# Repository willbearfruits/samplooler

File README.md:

# Samplooler

A small looper you play by tilting it. Hold the button and make a sound; let go and it loops. Tip
the box forward and the loop runs faster, tip it back and it runs backwards, roll it sideways for a
tape delay or a stutter.

> PHOTO: the Stack in a hand, tipped forward, screen lit (media/photos/stack-hand.jpg)

**[Try it and flash it from the browser](https://willbearfruits.github.io/samplooler/)** ·
[Manual](docs/MANUAL.md) · [Build one](docs/BUILD.md) · [Get one](#get-one)

The loop is a tape between two reels, and a small operator runs on it, as fast as you tip the box. The screen
above is the firmware's own drawing code, run on a computer.

> VIDEO: someone playing a Stack, filmed, with its sound, about 60 s

## What it does

| | |
| - | - |
| Record | Hold the button and make a sound, up to 20 s at 32 kHz. Let go and it loops. |
| Tilt | Forward plays faster, back plays backwards. Snap rounds the speed to octaves and fifths. |
| Roll | Left adds a tape delay, right a stutter. |
| Modes | TAPE (speed and pitch move together) and GRAIN (they move apart). |
| Voice | Optional: SING's 18 voices on the input before it records (autotune, harmonies, choir, vocoder, echo). |
| Speaker | Can be switched off, so only the line out plays, when the speaker feeds back into the mic. |
| Slots | 8 loops saved on the board, kept when you update it. |
| Together | Over the radio with the other instruments: a take sets their tempo or lands on their beat; key and scale are shared. |
| With a computer | USB MIDI and a USB sound card on one cable, and a VST3 plugin that shows and sets everything. |
| Other instruments | More firmwares for the same box: a breakcore-to-doom machine, a singing Buddha with a wall of amps, a flute you blow. |

## Other instruments

The same Stack can be flashed with [WRECK](instruments/wreck), [MANTRA](instruments/mantra) or
[HUFF](instruments/huff), and flashed back. Install them from the [page](https://willbearfruits.github.io/samplooler/#instruments)
or with the desktop app in [app/](app/). More are in progress ([instruments/](instruments/), [ROADMAP.md](ROADMAP.md)).
Anyone can add one ([CONTRIBUTING.md](CONTRIBUTING.md)).

## Get one

- **Buy one**: built by hand in Haifa. Write and ask about price and shipping:
  [Dogme84@gmail.com](mailto:Dogme84@gmail.com?subject=Samplooler) ·
  [WhatsApp](https://wa.me/972539263808).
- **Build it in the workshop**: the [ESP32 workshop](https://willbearfruits.github.io/serious-shit/workshop-esp32.html),
  7 meetings at MEZO, Haifa, 2,200 ₪, kit included.
- **Build it yourself**: order the boards, solder the modules on, flash it: [docs/BUILD.md](docs/BUILD.md).

## Status

Early. The current Stack is rev C: it has been made and runs the firmware (screen, microphone, tilt,
line out and USB MIDI/audio work). The board files here are rev D, which is being tested now (October
2026); rev C's files are at the git tag `checkpoint/boards-rev-c`. The three other instruments on the list have run
on a board; eight more are in progress. What comes next is in [ROADMAP.md](ROADMAP.md). Reports of builds, good or
bad, are welcome in the issues.

## What is where

| Path | What |
| - | - |
| [ROADMAP.md](ROADMAP.md) | what is done and what comes next |
| [docs/](docs/) | the manual and the build guide |
| [firmware/](firmware/) | the Samplooler's ESP-IDF 5.5 project |
| [instruments/](instruments/) | the other instruments, each a complete ESP-IDF project |
| [core/](core/) | the code the instruments share |
| [hardware/](hardware/) | the Stack's schematics, boards and JLCPCB order files |
| [plugin/](plugin/) | the VST3 and standalone plugin (JUCE) |
| [app/](app/) | the desktop app: the library, one-click install of any instrument on a board, and the Samplooler back |
| [media/](media/) | pictures and screen grabs |
| [site/](site/) | the project page and the browser flasher |
| [tools/](tools/) | `flash.sh`, `sl_midi.py` (log and MIDI from a shell), `release.sh`, `library.py` |

## Licence

- Firmware, instruments and tools: GPL-3.0 ([LICENSE](LICENSE)).
- Plugin: AGPL-3.0, as JUCE requires ([plugin/LICENSE](plugin/LICENSE)).
- Circuit boards, docs and pictures: CC BY-SA 4.0 ([hardware/LICENSE](hardware/LICENSE)).

---

Part of [Serious S.H.I.T.](https://willbearfruits.github.io/): instruments, tools and workshops made in Haifa by
Yaniv Schonfeld (Willbear). If Samplooler is useful to you, [support it on Patreon](https://www.patreon.com/Seriousshit).

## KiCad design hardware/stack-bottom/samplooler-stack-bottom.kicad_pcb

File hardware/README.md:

# Samplooler Stack boards

Two boards, 94 x 46 mm, 11 mm apart on M3 standoffs, made as one 94 x 94 mm panel. The bottom board carries every
module, the bare joystick and the encoder. The top board hangs the OLED and the microphone underneath it, seen and
heard through a window and a port. The modules sit on straight headers; the pins follow `firmware/main/pins.h`.

Rev C is the current board: it was made and runs the firmware, and the screen, microphone, tilt, line out and USB
MIDI/audio work. Its files are at the git tag `checkpoint/boards-rev-c`. Rev C has the KY-023 joystick on its own
little board, DAC strap jumpers, and the OLED and the mic on top of the top board. The files here are rev D, which
is being tested now (October 2026).

Both rev D boards pass ERC and DRC with no findings; the reports are in each project folder. How to build one is in
[docs/BUILD.md](../docs/BUILD.md).

## What is on each board

| Board | Ref | Part | Notes |
| - | - | - | - |
| Bottom | U1 | ESP32-S3 SuperMini (ESP32-S3FH4R2) | 20 pogo pads underneath |
| Bottom | U2 | GY-PCM5102 DAC with 3.5 mm jack | control pins tied on the board through its 9-pin row |
| Bottom | U4 | GY-521 (MPU-6050) | the tilt sensor |
| Bottom | U5 | PS2-style joystick, bare (the part on a KY-023) | its click is the record button (GPIO 3); X and Y go to GPIO 2 and 1, unused by the firmware |
| Bottom | SW1 | EC11 encoder with push, 25 mm shaft | |
| Bottom | J1 | 2 x 4 socket | the link to the top board: I2C for the OLED, I2S for the mic, GND |
| Bottom | J2 | header for a MAX98357A amp | optional |
| Bottom | J3 | Qwiic, JST-SH 4-pin | optional |
| Bottom | J4, J5 | EXP A, EXP B | breakouts, below |
| Bottom | C1 to C3 | 10 µF, 10 µF, 100 nF, 0805 | |
| Bottom | R1, R2 | 4.7 k I2C pull-ups, 0805 | not fitted |
| Top | U1 | SSD1306 0.96" OLED, 4 pins | underneath, seen through a window |
| Top | U2 | INMP441 microphone | underneath, hears through a 1.5 mm port |
| Top | J1 | 2 x 4 header | underneath, into the bottom board's socket |
| Top | JP1, JP2 | OLED pin-order jumpers | |
| Top | C1 to C3 | 10 µF, 100 nF, 100 nF, 0805 | |

The top board has openings for the stick, the encoder shaft, BOOT and RST. The full parts list with quantities is
in [docs/BUILD.md](../docs/BUILD.md#parts).

## Extras

| Extra | What it is |
| - | - |
| Pogo pins | Spring pins on the bottom board touch the SuperMini's 20 underside pads, for 20 more GPIOs: 14 to 18, 21, 33 to 42 and 45 to 48. They only feed the breakouts; the Samplooler does not need them. |
| EXP A, EXP B | Every GPIO the design does not use, on labelled 2.54 mm pads in the middle of the bottom board, under the top board. Solder wires, or fit plain straight headers (2.5 mm plastic plus about 6 mm of pin clears the 11 mm gap) and connect them before the top board goes on. There is no room for Dupont housings between the boards. |
| Qwiic | JST-SH, 3.3 V I2C, for sensors and add-ons. |
| Amp header | For the optional MAX98357A (Adafruit 3006 pin order), which hangs off the left edge. It takes 5 V. |
| OLED pin-order jumpers | JP1 and JP2 swap GND and VCC, so both common OLED pin orders fit without rework. |
| DAC pins tied | FLT, DEMP and FMT to ground, XSMT to the DAC's own 3.3 V, through the DAC's 9-pin row. No straps to set. |

EXP A, upper row, left to right; pin 1 is top right:

| | | | | | | | |
| - | :-: | :-: | :-: | :-: | :-: | :-: | :-: |
| top | GND | 48 | 47 | 46 | 42 | 40 | 43 TX |
| bottom | 3V3 | 37 | 38 | 45 | 41 | 39 | 44 RX |

EXP B, lower row, left to right; pin 1 is top right:

| | | | | | | | |
| - | :-: | :-: | :-: | :-: | :-: | :-: | :-: |
| top | GND | GND | 36 | 17 | 15 | 18 | 33 |
| bottom | 5V | 3V3 | 35 | 16 | 14 | 21 | 34 |

The numbers are not in order because each row takes the lines in the order they come out from under the SuperMini.

The SuperMini sits on its headers 2.5 mm above the board, and its pads are 1.753 mm apart down each column, so the
pogo pin's base width matters more than its height. You only need pins on the pads you use. Clamp the module while
you solder its headers: the springs push it up.

| Pogo pin | Fits | Where |
| - | - | - |
| Same Sky CPG-15-SMT-TR | every pad | DigiKey, Same Sky; not at LCSC |
| SMD pogo pins with a 2 mm flange, e.g. YIYUAN (LCSC C5221287, C2988082, C5157384) | every other pad only | LCSC |
| Harwin P70 (LCSC C17702549), Mill-Max 0900 | only with a spacer: they don't match the 2.5 mm gap | |

Two checks on your own SuperMini. The silkscreen of the pad column next to TX/RX says 48 at the top and 39 at the
bottom, but nologo's schematic shows the reverse: meter it in diode mode, the pad marked 48 lights the module's RGB
LED. And GPIO 45 and 46 must not be pulled high at power-up (45 high sets the flash to 1.8 V).

## Pictures

| Bottom board | Top board |
| - | - |
|  |  |
|  |  |

| From the nose | The panel |
| - | - |
|  |  |

The back of the panel: [images/panel-stack-back.png](images/panel-stack-back.png). All renders, from KiCad.

> PHOTO: the rev D boards as made, both faces, bare and with the modules on

## Ordering from JLCPCB

The two boards come as one panel, 94 x 94 mm, so they fit JLC's 100 x 100 mm price. They are joined by three 5 mm
tabs across a 2 mm slot, each tab with a row of 0.5 mm mouse-bite holes on both sides: snap them apart and file the
nubs flush.

Upload `fab/samplooler-panel-stack-jlcpcb.zip`. Also set Panel by Customer, and Different Design to 2. JLC counts
two designs on one panel as a different-design order and may charge for it; check the price before you pay.

| Setting | Value |
| - | - |
| Layers | 2 |
| Thickness | 1.6 mm FR-4 |
| Surface | HASL lead-free, or ENIG |
| Tracks / vias | 0.25 mm signal, 0.5 to 0.6 mm power, 0.6/0.3 mm vias, 0.5 mm to the edge: the standard process |
| Order number | "Specify a location": each board carries a `JLCJLCJLCJLC` text on its back (the panel has two; JLC uses one) |

The encoder's mounting lugs are plated slots, which the standard process covers. The openings for the stick, the
shaft, BOOT and RST, and the screen's window, are routed from the outline.

The SMD parts are the 0805 capacitors, the two unfitted 0805 resistors and the pogo pins. The capacitors are easy
by hand. If you'd rather have JLC fit them, the BOM and CPL files are in JLC's SMT format. The panel's pair names
each part with its board's prefix (`BC1` is the bottom board's C1, `TC1` the top's), and JLC may want tooling rails
added for assembly, which the panel doesn't have.

| File in `fab/` | What |
| - | - |
| [samplooler-panel-stack-jlcpcb.zip](fab/samplooler-panel-stack-jlcpcb.zip) | Gerbers and drill files for the panel, both boards. The one to upload. |
| [samplooler-panel-stack-bom.csv](fab/samplooler-panel-stack-bom.csv), [-cpl.csv](fab/samplooler-panel-stack-cpl.csv) | the panel's capacitors, for JLC assembly |
| [samplooler-stack-bottom-jlcpcb.zip](fab/samplooler-stack-bottom-jlcpcb.zip), [samplooler-stack-top-jlcpcb.zip](fab/samplooler-stack-top-jlcpcb.zip) | each board on its own |
| [samplooler-stack-bottom-bom.csv](fab/samplooler-stack-bottom-bom.csv), [-cpl.csv](fab/samplooler-stack-bottom-cpl.csv) | the bottom board's capacitors |
| [samplooler-stack-top-bom.csv](fab/samplooler-stack-top-bom.csv), [-cpl.csv](fab/samplooler-stack-top-cpl.csv) | the top board's capacitors |
| [samplooler-stack-bottom-schematic.pdf](fab/samplooler-stack-bottom-schematic.pdf), [samplooler-stack-top-schematic.pdf](fab/samplooler-stack-top-schematic.pdf) | the schematics |

## Before you order: measure these

Cheap modules differ between sellers. Where sources disagreed, the pads sit at the midpoint and the drills are
opened up. A minute with calipers confirms these:

| Check | Designed for | Tolerance built in |
| - | - | - |
| SuperMini: distance between its two pin rows | 15.33 mm (sources say 15.24 to 15.46) | 1.1 mm drills fit either |
| DAC: the 9-pin row (FLT to LROUT) against the 6-pin header | 6.475 mm in, 0.65 mm up from SCK | 1.2 mm drills |
| OLED: pin order | GND VCC SCL SDA | the jumpers swap GND and VCC |
| OLED: active area against the header | 21.7 x 10.9 mm, its top edge 4.5 mm below the pins | window 1.5 mm larger all round (24.7 x 13.9 mm) |
| Joystick: switch legs | rows 7.81 and 12.6 mm from the stick, 6.35 mm apart across | 1.2 mm drills (Adafruit's footprint says 8.0 / 12.5, SparkFun's 7.62 / 12.7) |
| Joystick: from the bottom of its frame to the underside of the cap | 20 mm, an estimate: no maker drawing found | at full tilt (25 degrees) the cap's rim stays over the top board from about 18.5 mm (20 mm if it tilts 30 degrees); lower, and it can touch the board |

## Opening them in KiCad

KiCad 10. Each folder is a project; the module symbols, footprints and 3D models come from `lib/` through the
projects' own library tables.

| Folder | What |
| - | - |
| [stack-bottom/](stack-bottom/) | the bottom board: schematic, PCB, ERC and DRC reports |
| [stack-top/](stack-top/) | the top board: the same |
| [panel-stack/](panel-stack/) | the two boards on one panel, as ordered |
| [lib/](lib/) | the symbol, footprint and 3D-model libraries for the modules |

## Licence

The board files, renders and fab outputs are CC BY-SA 4.0 ([LICENSE](LICENSE)).

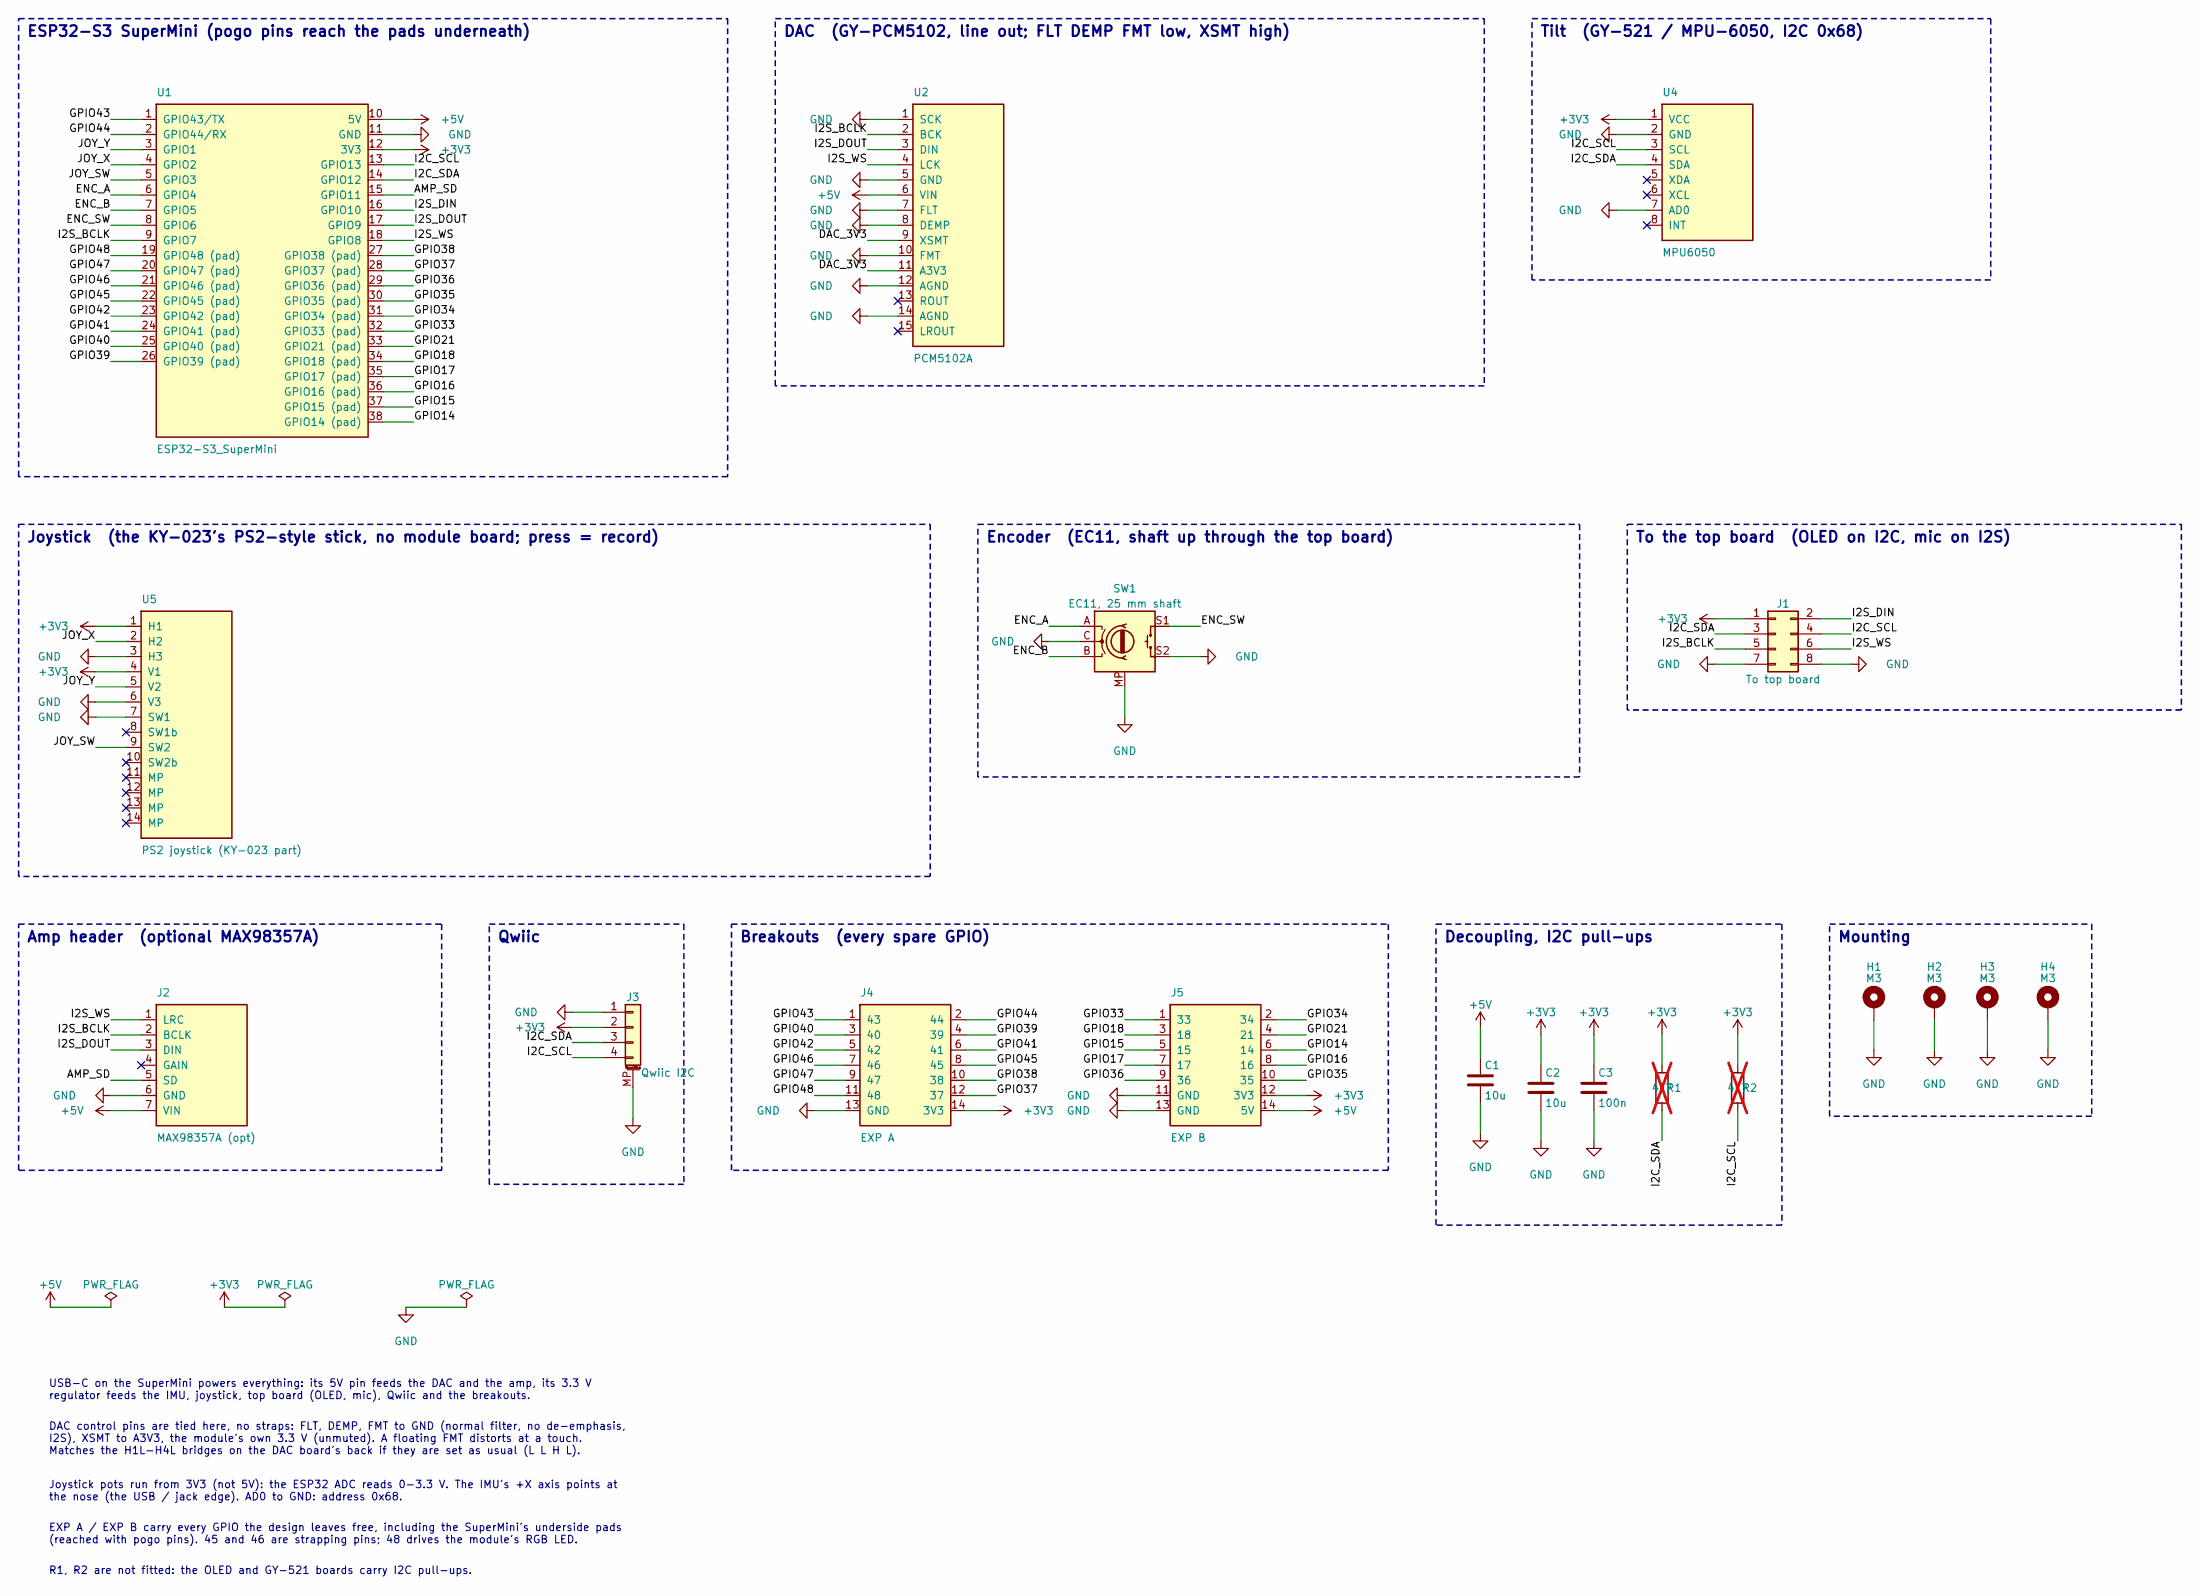
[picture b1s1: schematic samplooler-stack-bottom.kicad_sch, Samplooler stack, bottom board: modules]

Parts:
C1, C2: 10u; C_0805_2012Metric; LCSC C15850
C3: 100n; C_0805_2012Metric; LCSC C49678
H1, H2, H3, H4: M3; MountingHole_3.2mm_M3_Pad_Via
J1: To top board; PinSocket_2x04_P2.54mm_Vertical
J2: MAX98357A (opt); MAX98357A_Breakout
J3: Qwiic I2C; JST_SH_SM04B-SRSS-TB_1x04-1MP_P1.00mm_Horizontal
J4: EXP A; EXP_A_2x7_Stack
J5: EXP B; EXP_B_2x7_Stack
R1, R2: 4k7; R_0805_2012Metric; LCSC C17673; not fitted
SW1: EC11, 25 mm shaft; RotaryEncoder_Alps_EC11E-Switch_Vertical_H20mm
U1: ESP32-S3_SuperMini
U2: PCM5102A; GY-PCM5102
U4: MPU6050; GY-521_MPU6050
U5: PS2 joystick (KY-023 part); PS2_Joystick

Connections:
+3V3: C2.1, C3.1, J1.1, J3.2, J4.14 (3V3), J5.12 (3V3), R1.1, R2.1, U1.12 (3V3), U4.1 (VCC), U5.1 (H1), U5.4 (V1)
+5V: C1.1, J2.7 (VIN), J5.14 (5V), U1.10 (5V), U2.6 (VIN)
/AMP_SD: J2.5 (SD), U1.15 (11)
/DAC_3V3: U2.9 (XSMT), U2.11 (A3V3)
/ENC_A: SW1.A, U1.6 (4)
/ENC_B: SW1.B, U1.7 (5)
/ENC_SW: SW1.S1, U1.8 (6)
/GPIO14: J5.6 (14), U1.38 (GPIO14)
/GPIO15: J5.5 (15), U1.37 (GPIO15)
/GPIO16: J5.8 (16), U1.36 (GPIO16)
/GPIO17: J5.7 (17), U1.35 (GPIO17)
/GPIO18: J5.3 (18), U1.34 (GPIO18)
/GPIO21: J5.4 (21), U1.33 (GPIO21)
/GPIO33: J5.1 (33), U1.32 (GPIO33)
/GPIO34: J5.2 (34), U1.31 (GPIO34)
/GPIO35: J5.10 (35), U1.30 (GPIO35)
/GPIO36: J5.9 (36), U1.29 (GPIO36)
/GPIO37: J4.12 (37), U1.28 (GPIO37)
/GPIO38: J4.10 (38), U1.27 (GPIO38)
/GPIO39: J4.4 (39), U1.26 (GPIO39)
/GPIO40: J4.3 (40), U1.25 (GPIO40)
/GPIO41: J4.6 (41), U1.24 (GPIO41)
/GPIO42: J4.5 (42), U1.23 (GPIO42)
/GPIO43: J4.1 (43), U1.1 (TX)
/GPIO44: J4.2 (44), U1.2 (RX)
/GPIO45: J4.8 (45), U1.22 (GPIO45)
/GPIO46: J4.7 (46), U1.21 (GPIO46)
/GPIO47: J4.9 (47), U1.20 (GPIO47)
/GPIO48: J4.11 (48), U1.19 (GPIO48)
/I2C_SCL: J1.4, J3.4, R2.2, U1.13, U4.3 (SCL)
/I2C_SDA: J1.3, J3.3, R1.2, U1.14 (12), U4.4 (SDA)
/I2S_BCLK: J1.5, J2.2 (BCLK), U1.9 (7), U2.2 (BCK)
/I2S_DIN: J1.2, U1.16 (10)
/I2S_DOUT: J2.3 (DIN), U1.17 (9), U2.3 (DIN)
/I2S_WS: J1.6, J2.1 (LRC), U1.18 (8), U2.4 (LCK)
/JOY_SW: U1.5 (3), U5.9 (SW2)
/JOY_X: U1.4 (2), U5.2 (H2)
/JOY_Y: U1.3 (1), U5.5 (V2)
GND: C1.2, C2.2, C3.2, H1.1, H2.1, H3.1, H4.1, J1.7, J1.8, J2.6 (GND), J3.1, J3.MP (MountPin), J4.13 (GND), J5.11 (GND), J5.13 (GND), SW1.C, SW1.MP, SW1.S2, U1.11 (GND), U2.1 (SCK), U2.5 (GND), U2.7 (FLT), U2.8 (DEMP), U2.10 (FMT), U2.12 (AGND), U2.14 (AGND), U4.2 (GND), U4.7 (AD0), U5.3 (H3), U5.6 (V3), U5.7 (SW1)

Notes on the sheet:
ESP32-S3 SuperMini (pogo pins reach the pads underneath)
DAC (GY-PCM5102, line out; FLT DEMP FMT low, XSMT high)
Tilt (GY-521 / MPU-6050, I2C 0x68)
Joystick (the KY-023's PS2-style stick, no module board; press = record)
Encoder (EC11, shaft up through the top board)
To the top board (OLED on I2C, mic on I2S)
Amp header (optional MAX98357A)
Qwiic
Breakouts (every spare GPIO)
Decoupling, I2C pull-ups
Mounting
USB-C on the SuperMini powers everything: its 5V pin feeds the DAC and the amp, its 3.3 V regulator feeds the IMU, joystick, top board (OLED, mic), Qwiic and the breakouts.
DAC control pins are tied here, no straps: FLT, DEMP, FMT to GND (normal filter, no de-emphasis, I2S), XSMT to A3V3, the module's own 3.3 V (unmuted). A floating FMT distorts at a touch. Matches the H1L-H4L bridges on the DAC board's back if they are set as usual (L L H L).
Joystick pots run from 3V3 (not 5V): the ESP32 ADC reads 0-3.3 V. The IMU's +X axis points at the nose (the USB / jack edge). AD0 to GND: address 0x68.
EXP A / EXP B carry every GPIO the design leaves free, including the SuperMini's underside pads (reached with pogo pins). 45 and 46 are strapping pins; 48 drives the module's RGB LED.
R1, R2 are not fitted: the OLED and GY-521 boards carry I2C pull-ups.

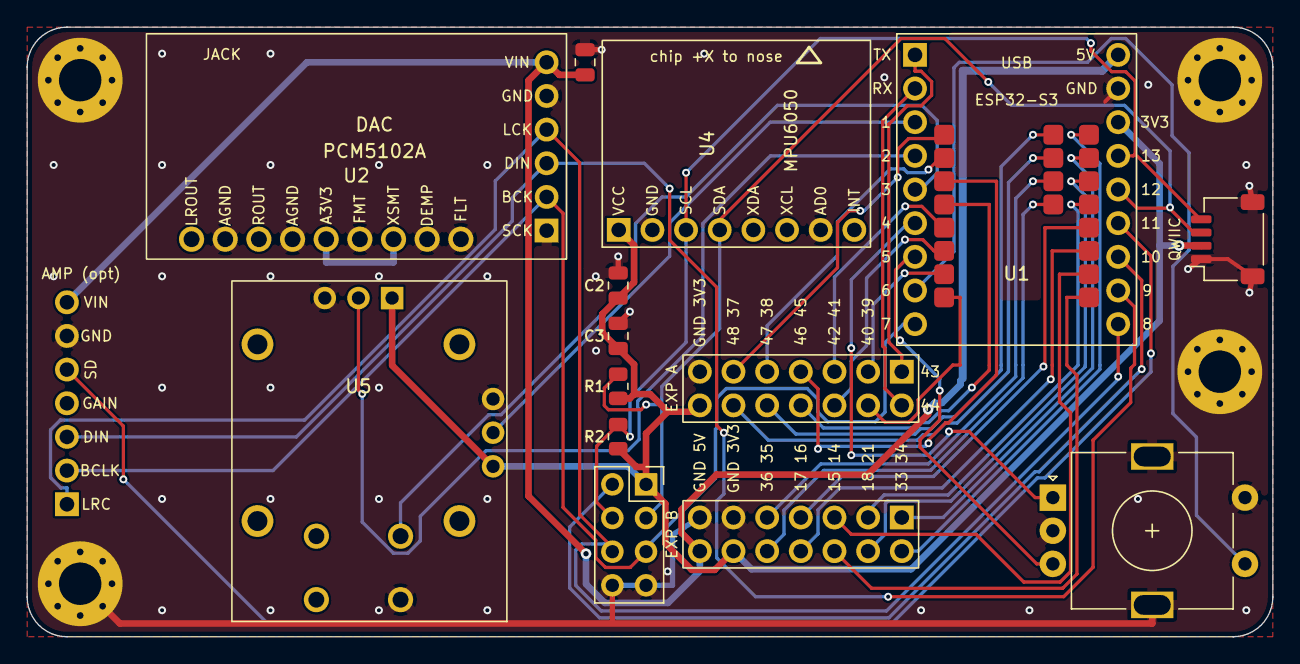
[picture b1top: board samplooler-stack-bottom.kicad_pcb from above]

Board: 2 copper layers, 94.0 x 46.0 mm, 19 parts (0 on the bottom side), 39 nets.

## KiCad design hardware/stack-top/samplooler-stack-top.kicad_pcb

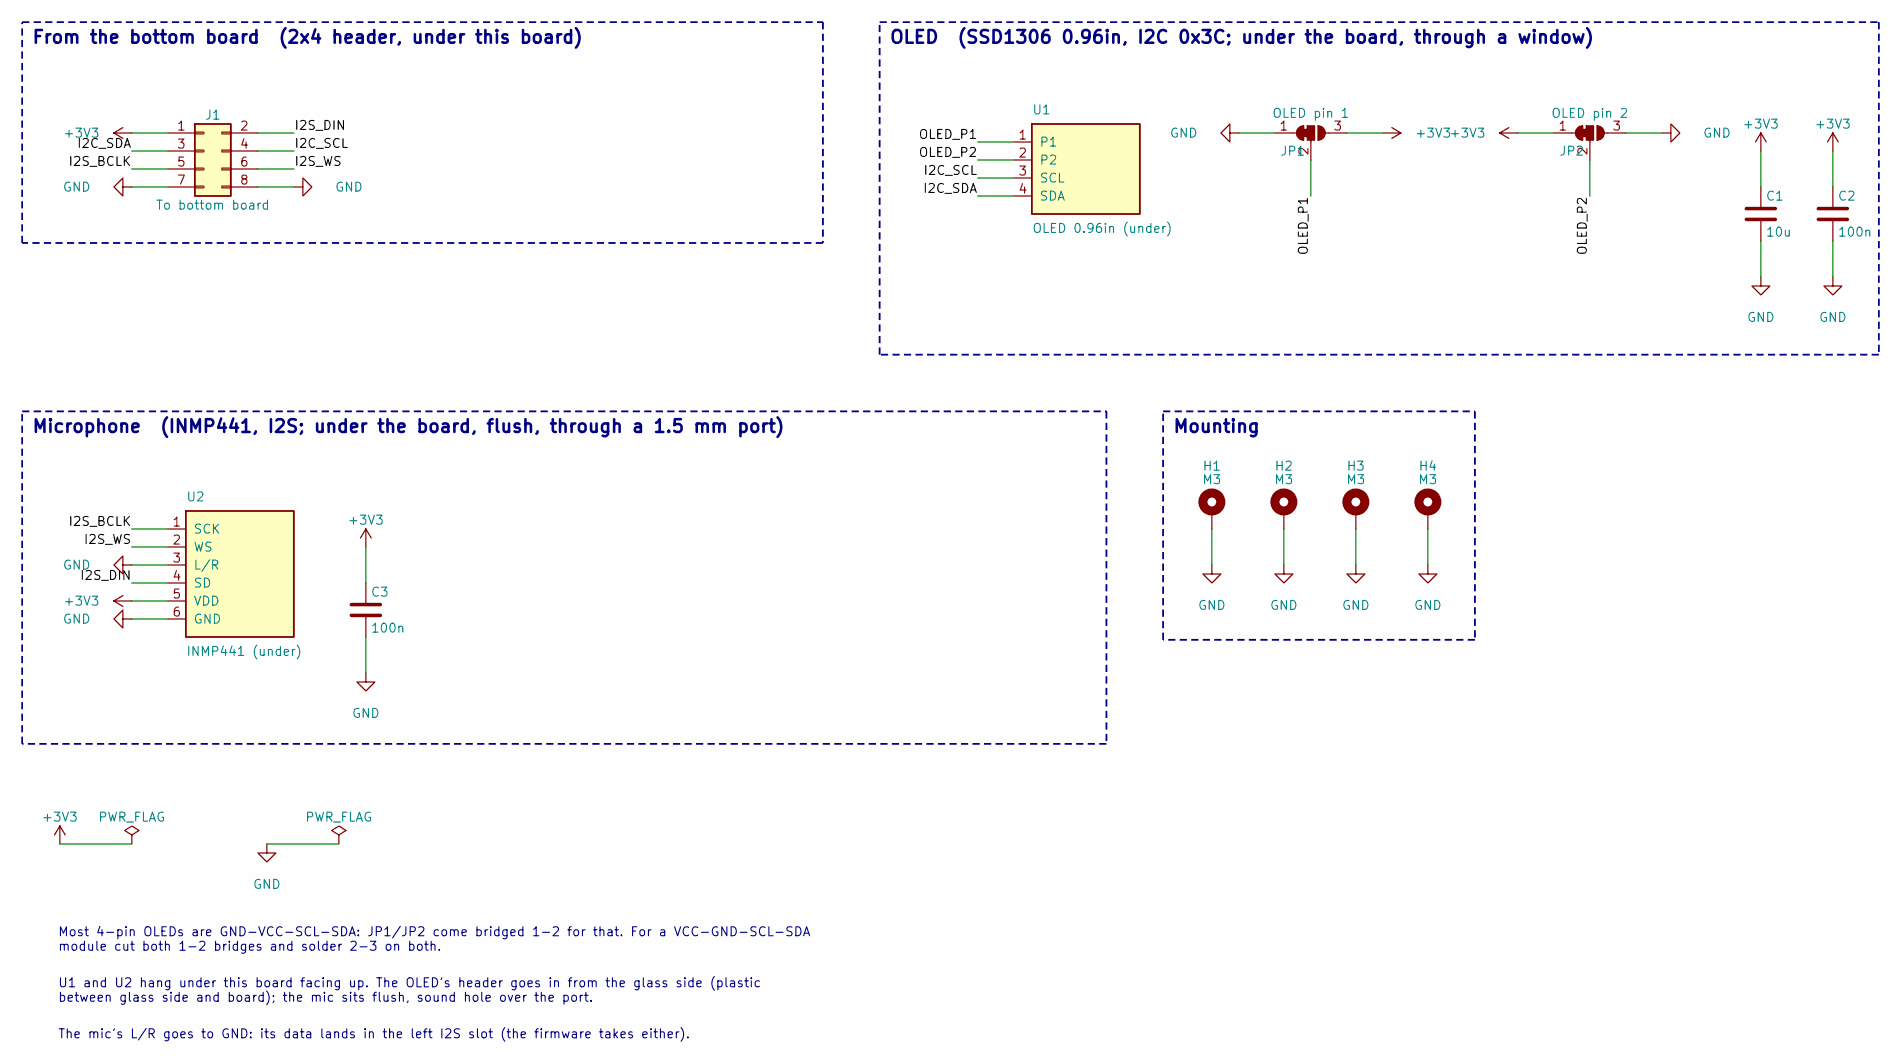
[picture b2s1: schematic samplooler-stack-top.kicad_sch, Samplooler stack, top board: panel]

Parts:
C1: 10u; C_0805_2012Metric; LCSC C15850
C2, C3: 100n; C_0805_2012Metric; LCSC C49678
H1, H2, H3, H4: M3; MountingHole_3.2mm_M3_Pad_Via
J1: To bottom board; PinHeader_2x04_P2.54mm_Vertical
JP1: OLED pin 1; SolderJumper-3_P1.3mm_Bridged12_RoundedPad1.0x1.5mm_NumberL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
JP2: OLED pin 2; SolderJumper-3_P1.3mm_Bridged12_RoundedPad1.0x1.5mm_NumberL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
U1: OLED 0.96in (under); SSD1306_0.96in_I2C_Under
U2: INMP441 (under); INMP441_Round_Under

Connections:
+3V3: C1.1, C2.1, C3.1, J1.1, JP1.3 (B), JP2.1 (A), U2.5 (VDD)
/I2C_SCL: J1.4, U1.3 (SCL)
/I2C_SDA: J1.3, U1.4 (SDA)
/I2S_BCLK: J1.5, U2.1 (SCK)
/I2S_DIN: J1.2, U2.4 (SD)
/I2S_WS: J1.6, U2.2 (WS)
/OLED_P1: JP1.2 (C), U1.1
/OLED_P2: JP2.2 (C), U1.2
GND: C1.2, C2.2, C3.2, H1.1, H2.1, H3.1, H4.1, J1.7, J1.8, JP1.1 (A), JP2.3 (B), U2.3 (L/R), U2.6 (GND)

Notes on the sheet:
From the bottom board (2x4 header, under this board)
OLED (SSD1306 0.96in, I2C 0x3C; under the board, through a window)
Microphone (INMP441, I2S; under the board, flush, through a 1.5 mm port)
Mounting
Most 4-pin OLEDs are GND-VCC-SCL-SDA: JP1/JP2 come bridged 1-2 for that. For a VCC-GND-SCL-SDA module cut both 1-2 bridges and solder 2-3 on both.
U1 and U2 hang under this board facing up. The OLED's header goes in from the glass side (plastic between glass side and board); the mic sits flush, sound hole over the port.
The mic's L/R goes to GND: its data lands in the left I2S slot (the firmware takes either).

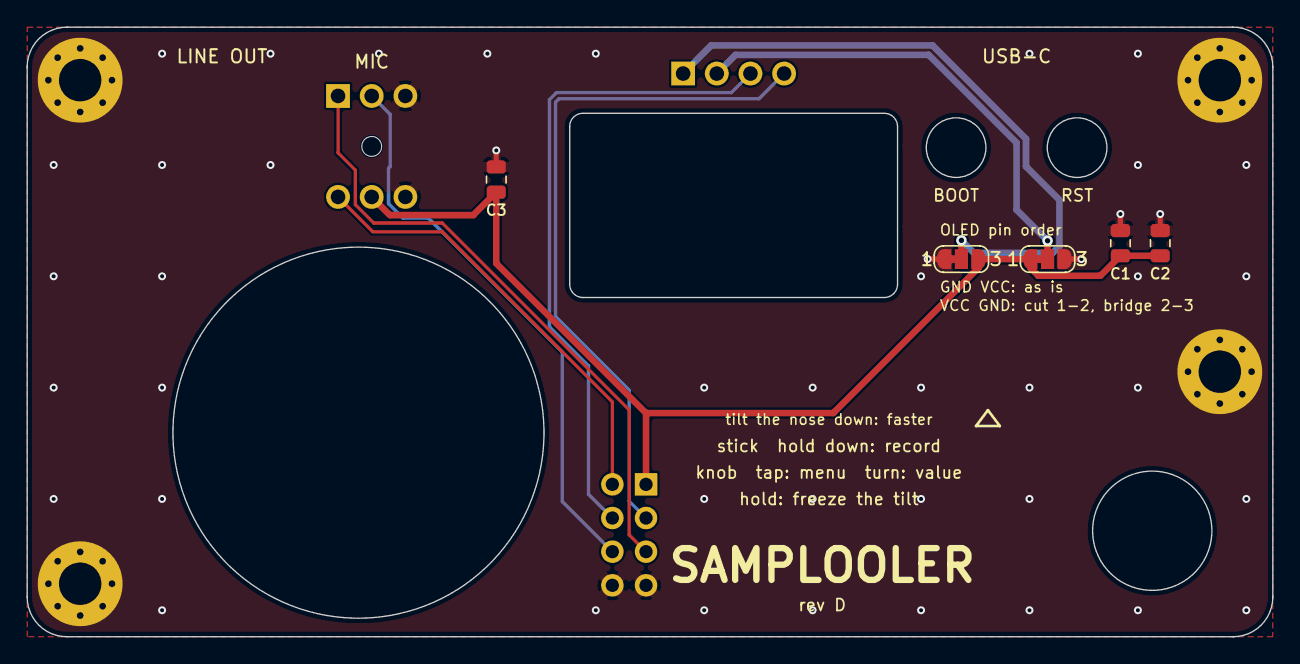
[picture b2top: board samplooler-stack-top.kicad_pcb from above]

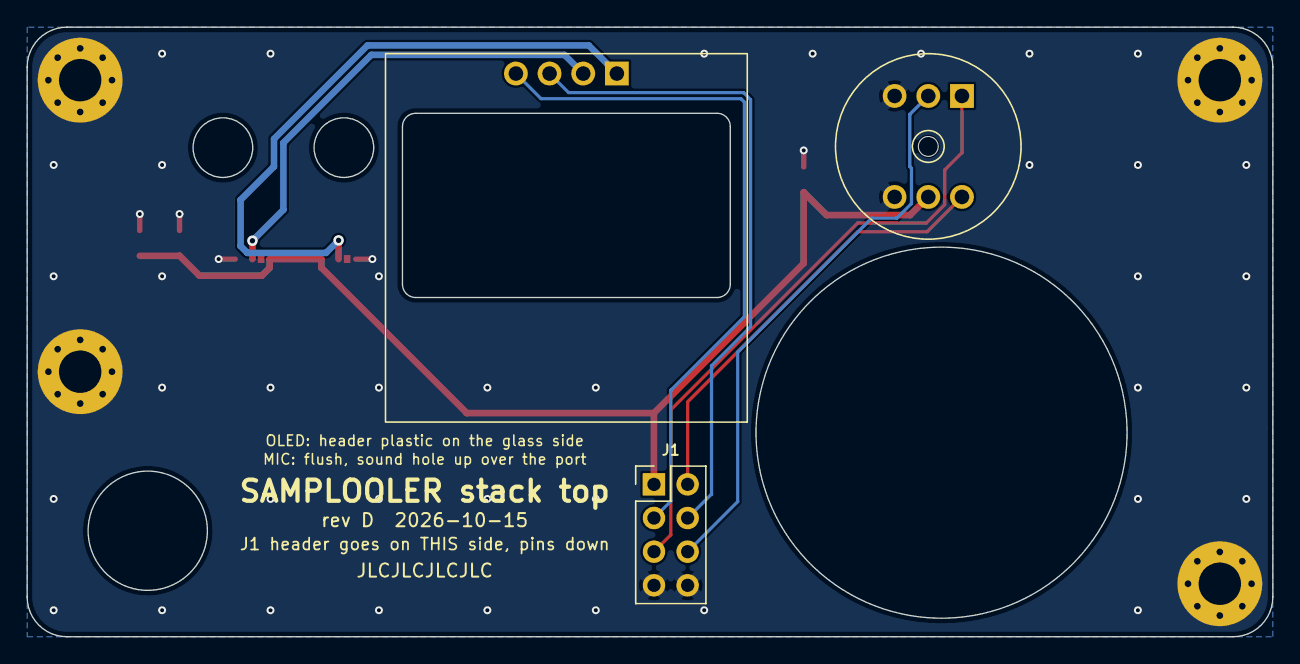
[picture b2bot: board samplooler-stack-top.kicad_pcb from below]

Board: 2 copper layers, 94.0 x 46.0 mm, 12 parts (3 on the bottom side), 9 nets.

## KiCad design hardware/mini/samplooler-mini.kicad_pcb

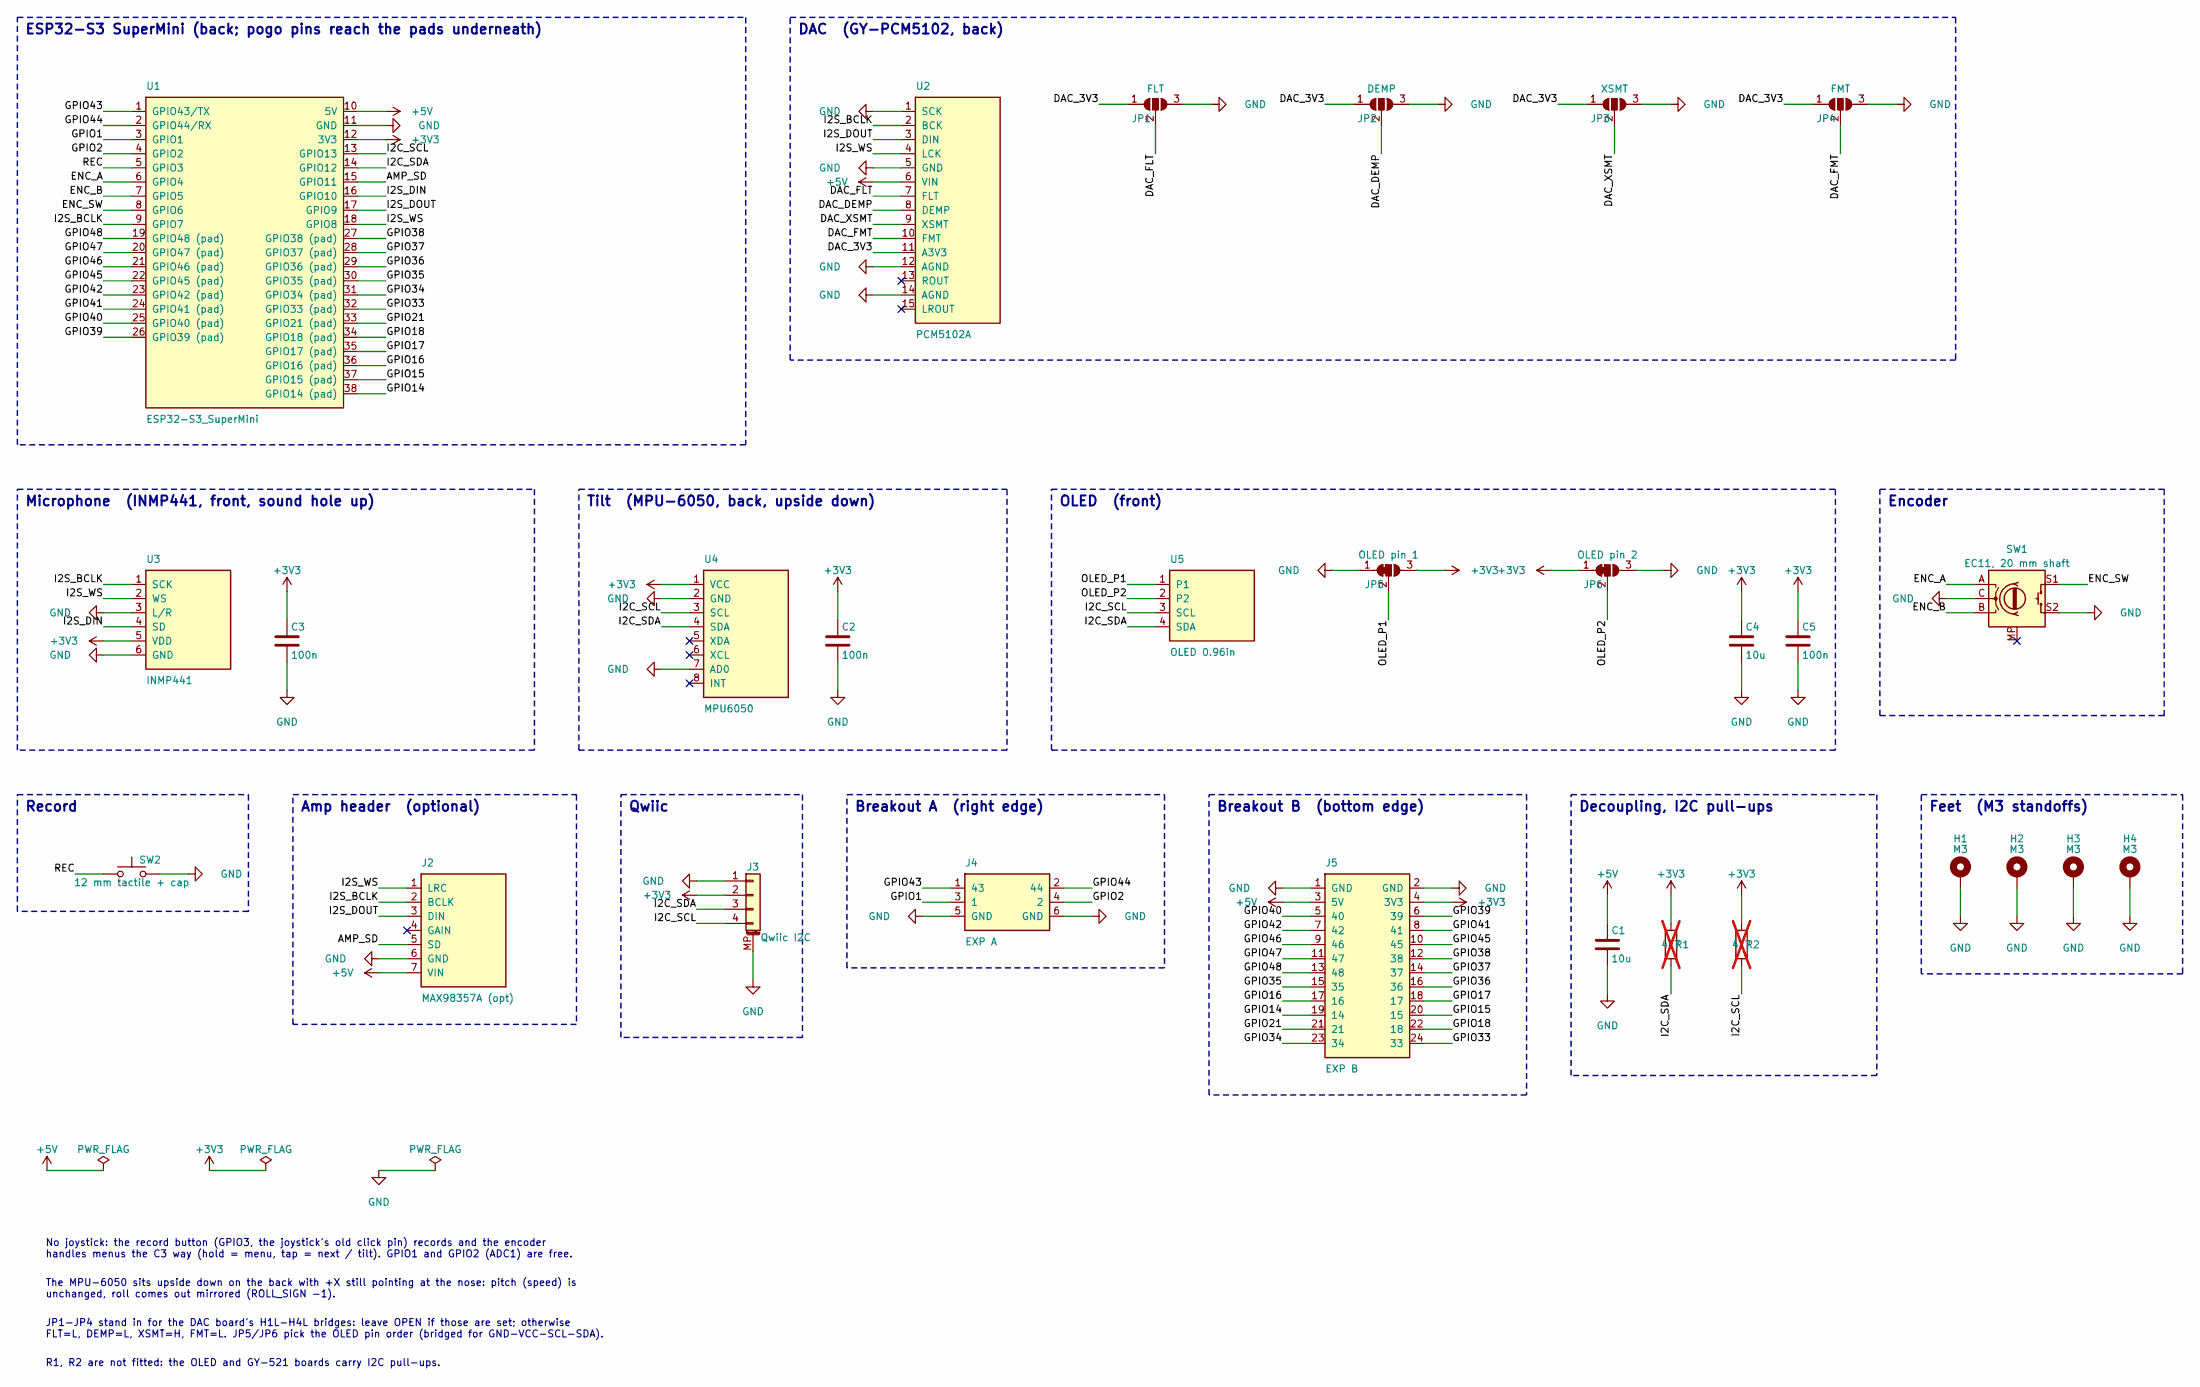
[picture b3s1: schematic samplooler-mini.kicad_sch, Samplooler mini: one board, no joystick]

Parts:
C1, C4: 10u; C_0805_2012Metric; LCSC C15850
C2, C3, C5: 100n; C_0805_2012Metric; LCSC C49678
H1, H2, H3, H4: M3; MountingHole_3.2mm_M3_Pad_Via
J2: MAX98357A (opt); MAX98357A_Breakout
J3: Qwiic I2C; JST_SH_SM04B-SRSS-TB_1x04-1MP_P1.00mm_Horizontal
J4: EXP A; EXP_A_2x3_Mini
J5: EXP B; EXP_B_2x12_Mini
JP1: FLT; SolderJumper-3_P1.3mm_Open_RoundedPad1.0x1.5mm
JP2: DEMP; SolderJumper-3_P1.3mm_Open_RoundedPad1.0x1.5mm
JP3: XSMT; SolderJumper-3_P1.3mm_Open_RoundedPad1.0x1.5mm
JP4: FMT; SolderJumper-3_P1.3mm_Open_RoundedPad1.0x1.5mm
JP5: OLED pin 1; SolderJumper-3_P1.3mm_Bridged12_RoundedPad1.0x1.5mm_NumberL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
JP6: OLED pin 2; SolderJumper-3_P1.3mm_Bridged12_RoundedPad1.0x1.5mm_NumberL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
R1, R2: 4k7; R_0805_2012Metric; LCSC C17673; not fitted
SW1: EC11, 20 mm shaft; RotaryEncoder_Alps_EC11E-Switch_Vertical_H20mm
SW2: 12 mm tactile + cap; SW_PUSH-12mm
U1: ESP32-S3_SuperMini
U2: PCM5102A; GY-PCM5102
U3: INMP441; INMP441_Round
U4: MPU6050; GY-521_MPU6050
U5: OLED 0.96in; SSD1306_0.96in_I2C_NoHoles

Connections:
+3V3: C2.1, C3.1, C4.1, C5.1, J3.2, J5.4 (3V3), JP5.3 (B), JP6.1 (A), R1.1, R2.1, U1.12 (3V3), U3.5 (VDD), U4.1 (VCC)
+5V: C1.1, J2.7 (VIN), J5.3 (5V), U1.10 (5V), U2.6 (VIN)
/AMP_SD: J2.5 (SD), U1.15 (11)
/DAC_3V3: JP1.1 (A), JP2.1 (A), JP3.1 (A), JP4.1 (A), U2.11 (A3V3)
/DAC_DEMP: JP2.2 (C), U2.8 (DEMP)
/DAC_FLT: JP1.2 (C), U2.7 (FLT)
/DAC_FMT: JP4.2 (C), U2.10 (FMT)
/DAC_XSMT: JP3.2 (C), U2.9 (XSMT)
/ENC_A: SW1.A, U1.6 (4)
/ENC_B: SW1.B, U1.7 (5)
/ENC_SW: SW1.S1, U1.8 (6)
/GPIO1: J4.3 (1), U1.3 (1)
/GPIO2: J4.4 (2), U1.4 (2)
/GPIO14: J5.19 (14), U1.38 (GPIO14)
/GPIO15: J5.20 (15), U1.37 (GPIO15)
/GPIO16: J5.17 (16), U1.36 (GPIO16)
/GPIO17: J5.18 (17), U1.35 (GPIO17)
/GPIO18: J5.22 (18), U1.34 (GPIO18)
/GPIO21: J5.21, U1.33 (GPIO21)
/GPIO33: J5.24 (33), U1.32 (GPIO33)
/GPIO34: J5.23 (34), U1.31 (GPIO34)
/GPIO35: J5.15 (35), U1.30 (GPIO35)
/GPIO36: J5.16 (36), U1.29 (GPIO36)
/GPIO37: J5.14 (37), U1.28 (GPIO37)
/GPIO38: J5.12 (38), U1.27 (GPIO38)
/GPIO39: J5.6 (39), U1.26 (GPIO39)
/GPIO40: J5.5 (40), U1.25 (GPIO40)
/GPIO41: J5.8 (41), U1.24 (GPIO41)
/GPIO42: J5.7 (42), U1.23 (GPIO42)
/GPIO43: J4.1 (43), U1.1 (TX)
/GPIO44: J4.2 (44), U1.2 (RX)
/GPIO45: J5.10 (45), U1.22 (GPIO45)
/GPIO46: J5.9 (46), U1.21 (GPIO46)
/GPIO47: J5.11 (47), U1.20 (GPIO47)
/GPIO48: J5.13 (48), U1.19 (GPIO48)
/I2C_SCL: J3.4, R2.2, U1.13, U4.3 (SCL), U5.3 (SCL)
/I2C_SDA: J3.3, R1.2, U1.14 (12), U4.4 (SDA), U5.4 (SDA)
/I2S_BCLK: J2.2 (BCLK), U1.9 (7), U2.2 (BCK), U3.1 (SCK)
/I2S_DIN: U1.16 (10), U3.4 (SD)
/I2S_DOUT: J2.3 (DIN), U1.17 (9), U2.3 (DIN)
/I2S_WS: J2.1 (LRC), U1.18 (8), U2.4 (LCK), U3.2 (WS)
/OLED_P1: JP5.2 (C), U5.1
/OLED_P2: JP6.2 (C), U5.2
/REC: SW2.1, U1.5 (3)
GND: C1.2, C2.2, C3.2, C4.2, C5.2, H1.1, H2.1, H3.1, H4.1, J2.6 (GND), J3.1, J3.MP (MountPin), J4.5 (GND), J4.6 (GND), J5.1 (GND), J5.2 (GND), JP1.3 (B), JP2.3 (B), JP3.3 (B), JP4.3 (B), JP5.1 (A), JP6.3 (B), SW1.C, SW1.S2, SW2.2, U1.11 (GND), U2.1 (SCK), U2.5 (GND), U2.12 (AGND), U2.14 (AGND), U3.3 (L/R), U3.6 (GND), U4.2 (GND), U4.7 (AD0)

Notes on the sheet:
ESP32-S3 SuperMini (back; pogo pins reach the pads underneath)
DAC (GY-PCM5102, back)
Microphone (INMP441, front, sound hole up)
Tilt (MPU-6050, back, upside down)
OLED (front)
Encoder
Record
Amp header (optional)
Qwiic
Breakout A (right edge)
Breakout B (bottom edge)
Decoupling, I2C pull-ups
Feet (M3 standoffs)
No joystick: the record button (GPIO3, the joystick's old click pin) records and the encoder handles menus the C3 way (hold = menu, tap = next / tilt). GPIO1 and GPIO2 (ADC1) are free.
The MPU-6050 sits upside down on the back with +X still pointing at the nose: pitch (speed) is unchanged, roll comes out mirrored (ROLL_SIGN -1).
JP1-JP4 stand in for the DAC board's H1L-H4L bridges: leave OPEN if those are set; otherwise FLT=L, DEMP=L, XSMT=H, FMT=L. JP5/JP6 pick the OLED pin order (bridged for GND-VCC-SCL-SDA).
R1, R2 are not fitted: the OLED and GY-521 boards carry I2C pull-ups.

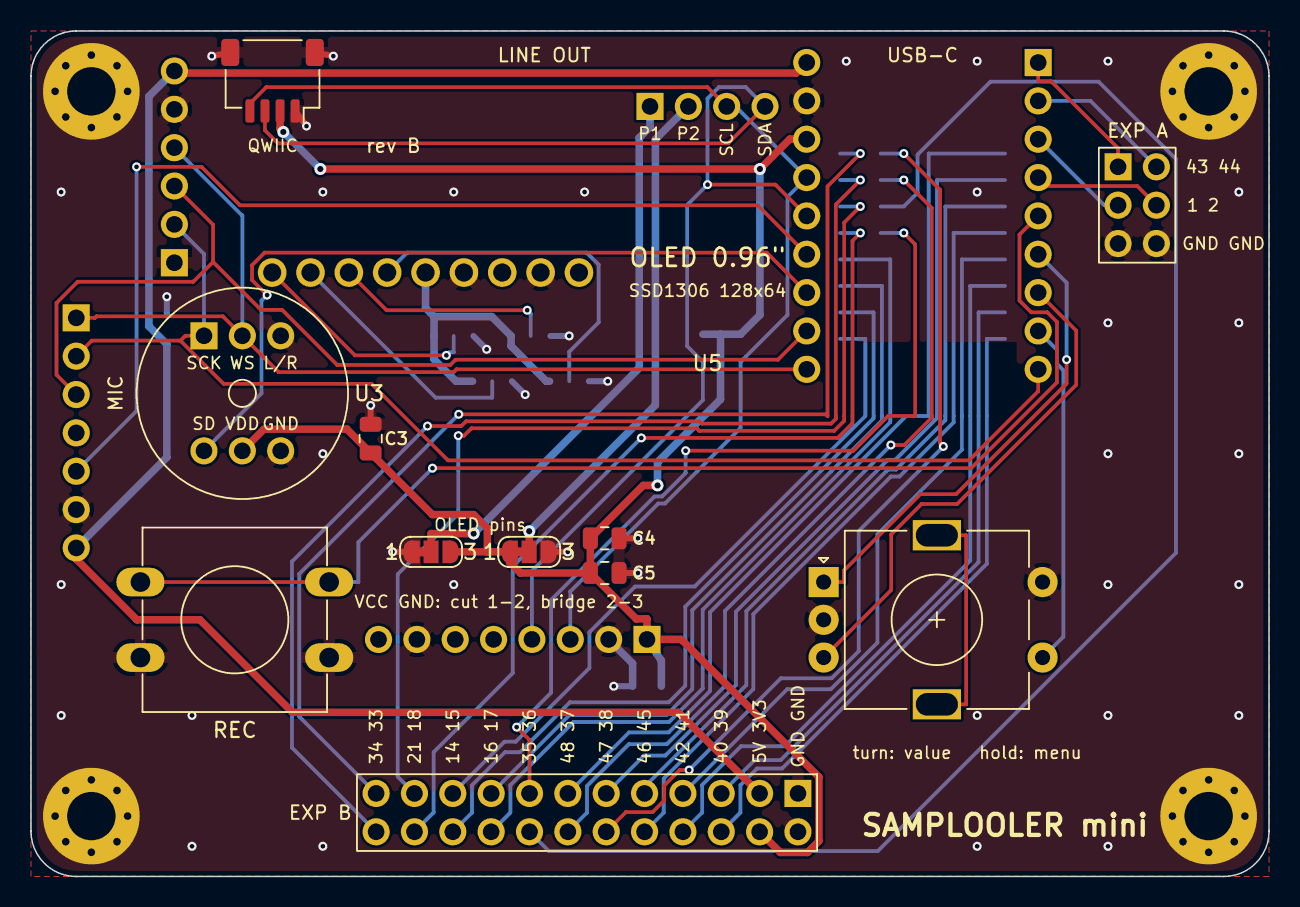
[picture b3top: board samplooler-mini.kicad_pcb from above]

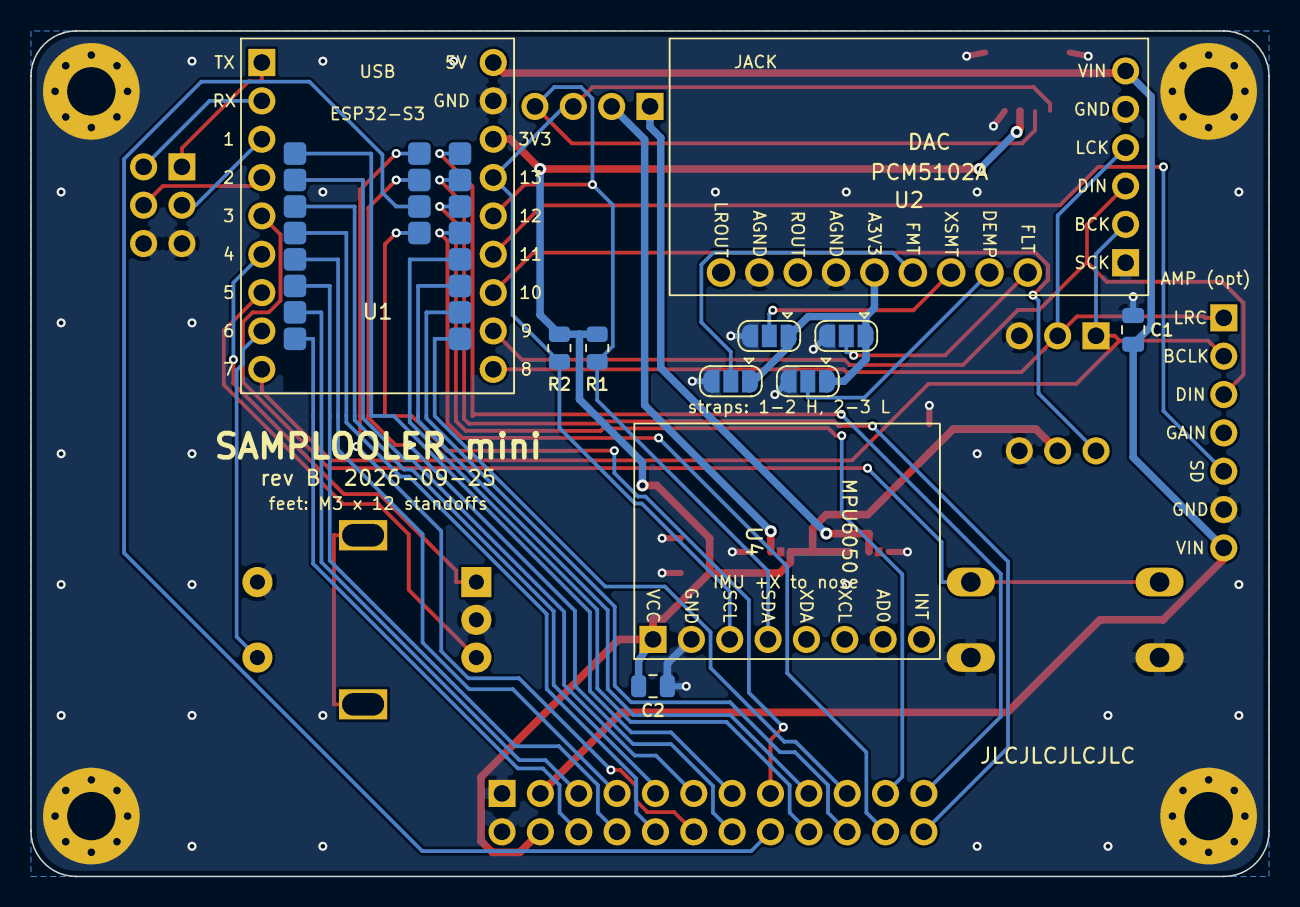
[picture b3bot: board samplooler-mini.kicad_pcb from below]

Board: 2 copper layers, 82.0 x 56.0 mm, 28 parts (12 on the bottom side), 45 nets.
